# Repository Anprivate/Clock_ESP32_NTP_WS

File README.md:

# Clock ESP32 NTP WS2812B
Wall clock on ESP32 with NTP synchronization and indicator on WS2812B

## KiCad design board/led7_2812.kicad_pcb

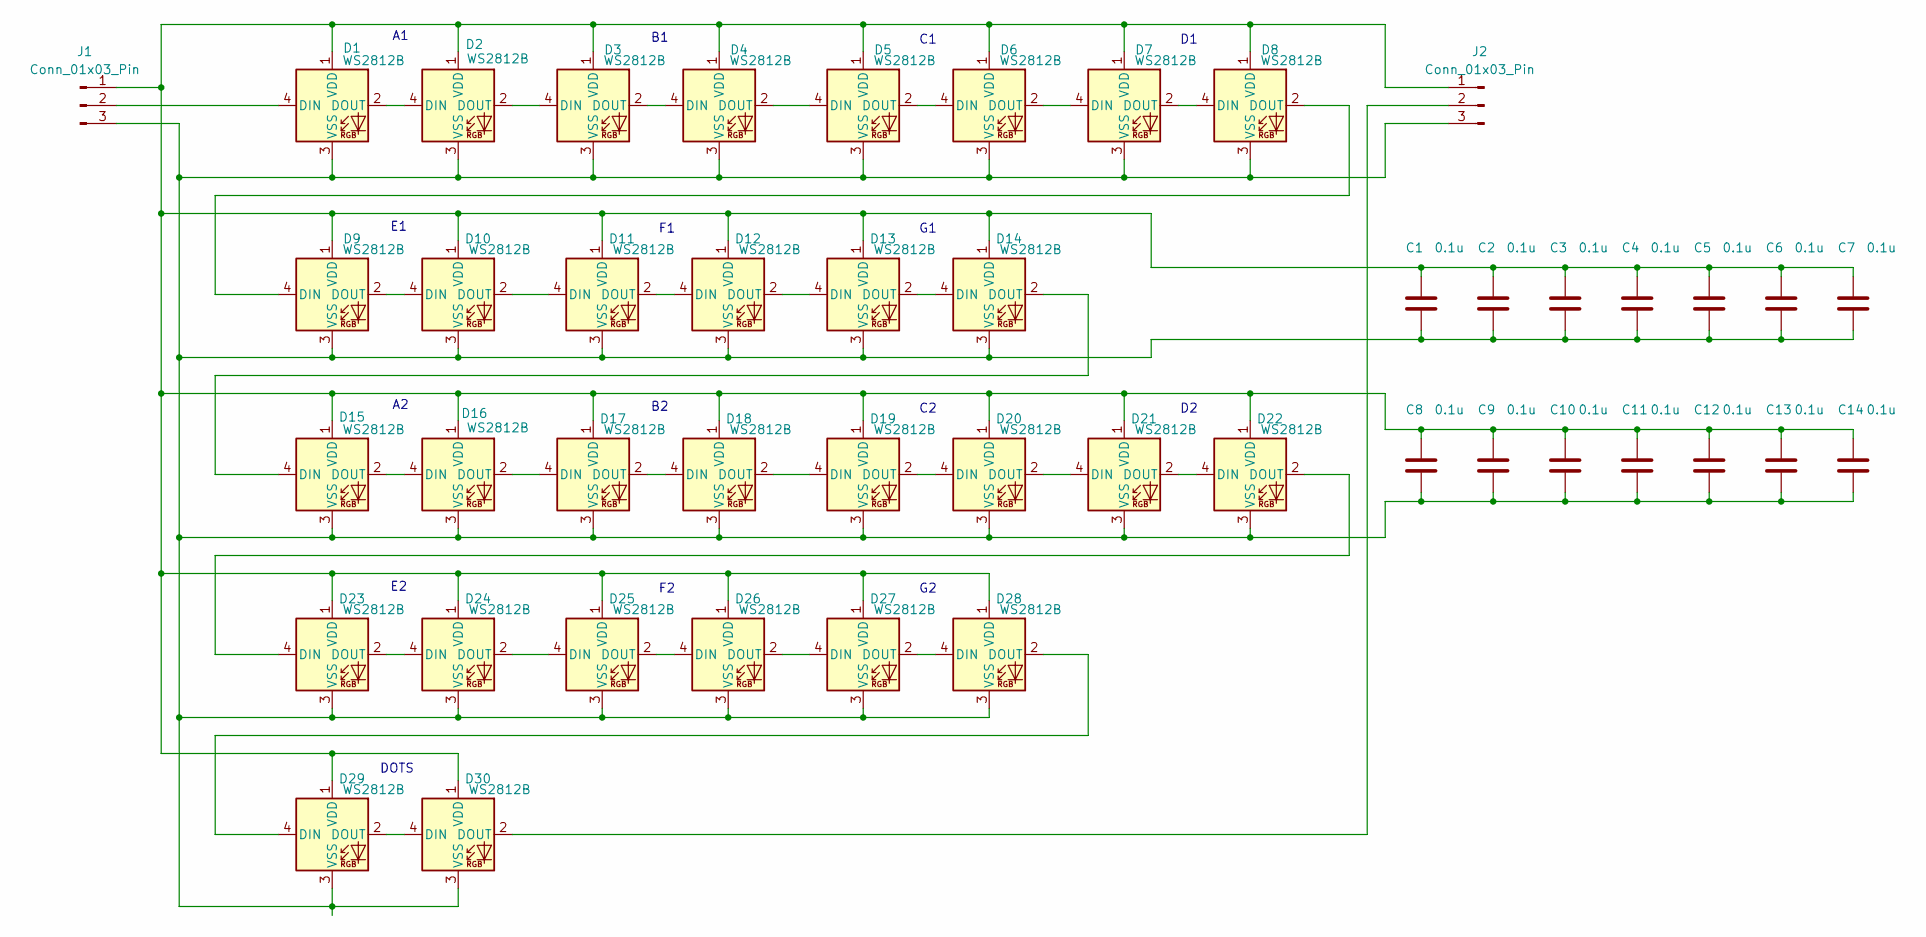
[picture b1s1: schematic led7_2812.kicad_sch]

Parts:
C1, C2, C3, C4, C5, C6, C7, C8, C9, C10, C11, C12, C13, C14: 0.1u; C_0805_2012Metric_Pad1.18x1.45mm_HandSolder
D1, D2, D3, D4, D5, D6, D7, D8, D9, D10, D11, D12, D13, D14, D15, D16, D17, D18, D19, D20, D21, D22, D23, D24, D25, D26, D27, D28, D29, D30: WS2812B; LED_Custom_ws2812
J1, J2: Conn_01x03_Pin; PinHeader_1x03_P2.54mm_Vertical

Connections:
unnamed: D1.4 (DIN), J1.2
unnamed: D1.2 (DOUT), D2.4 (DIN)
unnamed: C1.1, C2.1, C3.1, C4.1, C5.1, C6.1, C7.1, C8.1, C9.1, C10.1, C11.1, C12.1, C13.1, C14.1, D1.1 (VDD), D2.1 (VDD), D3.1 (VDD), D4.1 (VDD), D5.1 (VDD), D6.1 (VDD), D7.1 (VDD), D8.1 (VDD), D9.1 (VDD), D10.1 (VDD), D11.1 (VDD), D12.1 (VDD), D13.1 (VDD), D14.1 (VDD), D15.1 (VDD), D16.1 (VDD), D17.1 (VDD), D18.1 (VDD), D19.1 (VDD), D20.1 (VDD), D21.1 (VDD), D22.1 (VDD), D23.1 (VDD), D24.1 (VDD), D25.1 (VDD), D26.1 (VDD), D27.1 (VDD), D28.1 (VDD), D29.1 (VDD), D30.1 (VDD), J1.1, J2.1
unnamed: C1.2, C2.2, C3.2, C4.2, C5.2, C6.2, C7.2, C8.2, C9.2, C10.2, C11.2, C12.2, C13.2, C14.2, D1.3 (VSS), D2.3 (VSS), D3.3 (VSS), D4.3 (VSS), D5.3 (VSS), D6.3 (VSS), D7.3 (VSS), D8.3 (VSS), D9.3 (VSS), D10.3 (VSS), D11.3 (VSS), D12.3 (VSS), D13.3 (VSS), D14.3 (VSS), D15.3 (VSS), D16.3 (VSS), D17.3 (VSS), D18.3 (VSS), D19.3 (VSS), D20.3 (VSS), D21.3 (VSS), D22.3 (VSS), D23.3 (VSS), D24.3 (VSS), D25.3 (VSS), D26.3 (VSS), D27.3 (VSS), D28.3 (VSS), D29.3 (VSS), D30.3 (VSS), J1.3, J2.3
unnamed: D2.2 (DOUT), D3.4 (DIN)
unnamed: D3.2 (DOUT), D4.4 (DIN)
unnamed: D4.2 (DOUT), D5.4 (DIN)
unnamed: D5.2 (DOUT), D6.4 (DIN)
unnamed: D6.2 (DOUT), D7.4 (DIN)
unnamed: D7.2 (DOUT), D8.4 (DIN)
unnamed: D8.2 (DOUT), D9.4 (DIN)
unnamed: D9.2 (DOUT), D10.4 (DIN)
unnamed: D10.2 (DOUT), D11.4 (DIN)
unnamed: D11.2 (DOUT), D12.4 (DIN)
unnamed: D12.2 (DOUT), D13.4 (DIN)
unnamed: D13.2 (DOUT), D14.4 (DIN)
unnamed: D14.2 (DOUT), D15.4 (DIN)
unnamed: D15.2 (DOUT), D16.4 (DIN)
unnamed: D16.2 (DOUT), D17.4 (DIN)
unnamed: D17.2 (DOUT), D18.4 (DIN)
unnamed: D18.2 (DOUT), D19.4 (DIN)
unnamed: D19.2 (DOUT), D20.4 (DIN)
unnamed: D20.2 (DOUT), D21.4 (DIN)
unnamed: D21.2 (DOUT), D22.4 (DIN)
unnamed: D22.2 (DOUT), D23.4 (DIN)
unnamed: D23.2 (DOUT), D24.4 (DIN)
unnamed: D24.2 (DOUT), D25.4 (DIN)
unnamed: D25.2 (DOUT), D26.4 (DIN)
unnamed: D26.2 (DOUT), D27.4 (DIN)
unnamed: D27.2 (DOUT), D28.4 (DIN)
unnamed: D28.2 (DOUT), D29.4 (DIN)
unnamed: D29.2 (DOUT), D30.4 (DIN)
unnamed: D30.2 (DOUT), J2.2

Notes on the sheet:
DOTS

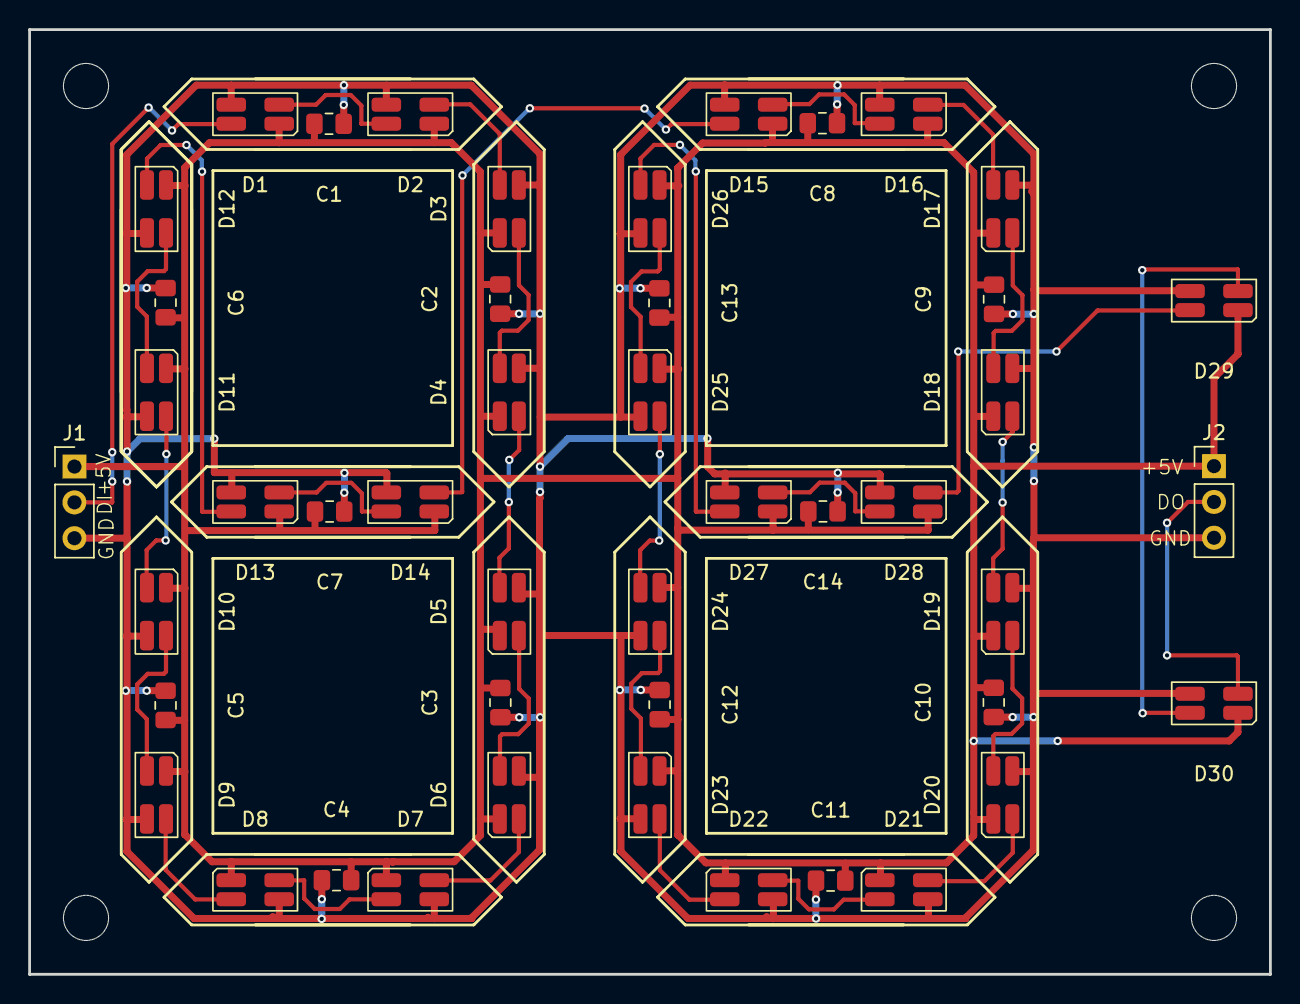
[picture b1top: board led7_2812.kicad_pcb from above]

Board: 2 copper layers, 88.0 x 67.0 mm, 46 parts (0 on the bottom side), 33 nets.

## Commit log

2025-08-07 Create tmp
2025-08-07 Create sources
2025-08-07 Create tm
2025-08-07 Create t
2025-11-05 Update ntp_ws_clock.ino
    Correct mistakes and add wifi.reconnect on disconnection
2025-11-15 reconnect interval added
